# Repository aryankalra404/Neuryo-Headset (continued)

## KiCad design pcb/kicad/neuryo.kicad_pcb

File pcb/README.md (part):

# Neuryo EEG board, rev B (plan)

**Status (5th pass, 11 Nov 2026):** designed in KiCad 10 ([neuryo-rev-b/](neuryo-rev-b/)), ERC/DRC/netlist checked after every step, firmware written, order files drafted ([order-draft-do-not-order/](neuryo-rev-b/review/order-draft-do-not-order/)), **not ordered**: the owner's checks before paying are in [checklist section 9](neuryo-rev-b/REVIEW-CHECKLIST.md) ([5th-pass changes](neuryo-rev-b/CHANGES.md#5th-pass-11-nov-2026), [assembly notes and placement-preview list](neuryo-rev-b/ASSEMBLY.md)). Rev B copies the analog half of a proven open board and adds a ready-made ESP32 board. Rev A (30 Oct, the v3 board: Cyton circuit, auto-routed, 100 × 80 mm, DevKit on sockets) is removed from this folder; it is in the git history (commit `14b8c37` and earlier).

| Folder | What is in it |
|---|---|
| [neuryo-rev-b/](neuryo-rev-b/) | Rev B in KiCad 10: project, [change list](neuryo-rev-b/CHANGES.md), [review checklist](neuryo-rev-b/REVIEW-CHECKLIST.md), renders, ERC/DRC reports, netlist and copper diffs against the reference, the reference imported into KiCad, and the scripts that made the edits |
| [low-cost-eeg/](low-cost-eeg/) | The upstream repo, complete (hardware, production files, firmware, receiver, case STLs, docs). The design rev B copies: [Low-Cost-EEG](https://github.com/XavierAsghar/Low-Cost-EEG) by Xavier Asghar, commit `3730d31` (12 Aug 2026). GPL-3.0 ([LICENSE](low-cost-eeg/LICENSE)); what was left out is listed in its [NOTICE](low-cost-eeg/NOTICE.md). **Do not order from `low-cost-eeg/Production_Files/NC Drill` as it is:** its drill coordinates are offset from the Gerbers (round-hole centres span x 64.4–158.9 mm, y 51.7–97.9 mm, while the Gerber outline is 0–100 × 0–50 mm) |

## Why this board
- **Same chips as ours:** ADS1299 (8 channels, SRB2 reference, bias drive) and an ESP32-S3, battery powered, 4-layer.
- **Built and used:** it recorded ECG, EMG, eyes-closed alpha, SSVEPs and P300s (Final Report, chapter 5), and a second person [rebuilt it](https://github.com/agteo/diy-eeg-mac) from the same files and recorded alpha.
- **Measured:** 1.10 µVpp input-referred noise with the inputs shorted, on the board itself (Final Report, section 6.1; the 2 µVpp earlier in the report is TI's evaluation board). The ADS1299 datasheet gives 1.13 µVpp typical at gain 12, 250 SPS.
- **Its analog section follows the OpenBCI Cyton**, like rev A did.

## What rev B copies unchanged (the analog half, about 55 × 50 mm)
In the KiCad rev B the analog half (x < 56 mm) and the LM27762 block are unchanged apart from the review changes; the TPS7A20 and its two capacitors had to be re-laid out in a strip under the LM27762 block (see [CHANGES B4](neuryo-rev-b/CHANGES.md)).

Placement, routing, ground pours and stitching kept as in the reference, left half of its board:
- Electrode inputs: 2.54 mm pin headers, 8 differential pairs, BIAS, SRB2.
- TPD4E1B06 ESD diodes, then 2.2 kΩ + 1 nF C0G low-pass on every input.
- ADS1299 with its decoupling, bipolar ±2.5 V mode.
- LM27762 charge-pump LDO for ±2.5 V; TPS7A20 low-noise LDO giving the ADS1299 its own 3.3 V.
- Stack-up: signal / ground / segmented power / signal; no split ground plane; analog left, digital right.

## What rev B changes (the digital half)
| Removed from the reference | Added in rev B |
|---|---|
| ESP32-S3-WROOM-1 and its 3.3 V LDO | Seeed XIAO ESP32-S3, soldered flat on castellated pads (Seeed's KiCad footprint); its 3V3 feeds the digital parts |
| USB-C, USB ESD, boot and reset buttons | The XIAO's own USB-C and buttons |
| USB / battery selector switch | Battery on/off slide switch (C&K PCM12, right edge); battery JST-PH (right edge) to the XIAO's BAT pads (the XIAO charges it) and to the LM27762 and TPS7A20 inputs |
| UART header | J6: earlobe MAX30102 and J7: BMI270, 1×4 headers on one I²C bus (the forehead MAX30102 header J8 was dropped) |
| | Battery divider (2 × 220 kΩ + 100 nF) to an ADC pin; USB-present divider; USB interlock (Q1, R37, R38) |
| | Outline 77 × 50 mm (the LM27762 block is kept in place, so 70 was not reachable), 2 mounting holes, for the v6 left pod |

## XIAO pin map
Final map in [neuryo-rev-b/CHANGES.md](neuryo-rev-b/CHANGES.md#final-xiao-pin-map-replaces-the-draft-in-pcbreadmemd). SPI on D1–D5 (330 Ω in series on SCLK, MOSI, CS since the 4th pass), battery on D0, I²C on D7/D8 (4.7 k pull-ups), USB sense on D9, ADS1299 RESET on D10 (4th pass); START and PWDN are tied (change 4).

## Review (8 Nov 2026): changes needed before ordering
Checked against the reference schematic and firmware (upstream `main.cpp`), the ADS1299 datasheet and the Seeed XIAO ESP32-S3 wiki.

| # | Change | Why |
|---|---|---|
| 1 | **Reference through SRB2, filtered.** Move R27 (2.2 kΩ) and C31 (1 nF) from SRB1 (pin 17) to SRB2 (pin 18, the next pin); leave SRB1 open and drop the header's direct SRB2 line. | On the reference, the REF header goes through R27/C31 to SRB1, but its SRB2 pin runs straight to the ADS1299 with no series resistor or filter. Upstream firmware uses SRB1 (MISC1 = 0x20, electrodes on the P inputs). D25 needs SRB2 so channel 8 can run differential (ECG). |
| 2 | **Analog off while USB is plugged in.** XIAO 5V pin → 2N7002 gate (100 kΩ to ground); its drain pulls the LM27762 EN+/EN− and TPS7A20 EN net (100 kΩ up to the battery) low. D9 (GPIO8) reads USB-present through a divider; firmware keeps the SPI pins high-impedance then. | Recording only on battery isolates the patient from mains. The XIAO's 5V pin is live only on USB (Seeed). The reference author lists this as the top-priority fix (Final Report 6.4). |
| 3 | **Charge batteries outside the headset.** Removable JST-PH cell, a separate charger and a spare. | The XIAO ESP32-S3 charges at 50 mA (Seeed), about 20 h for 1000 mAh. |
| 4 | **Pins with no XIAO GPIO:** START to ground through 10 kΩ (use the START command), RESET and PWDN to DVDD through 10 kΩ (RESET command), CLKSEL high as on the reference. Firmware sets BIASREF_INT = 1 (CONFIG3), as upstream does; the BIASREF pin is tied to AVSS on this board. | Datasheet: keep START low when using the command; mode pins through ≥ 10 kΩ. Upstream issue #1 (RESET on GPIO8 vs GPIO14) does not apply: rev B has no RESET GPIO. |
| 5 | **BIAS series resistor 51 kΩ** (R10, was 2.2 kΩ). Inputs stay 2.2 kΩ for the prototype; revisit with the test lab. | The bias amplifier can source 1.1 mA (datasheet) against DC patient-current limits of 10 µA normal and 50 µA single fault. TI's own figures show 51 kΩ patient-protection resistors. A 51 kΩ input resistor would add about 0.23 µVrms of noise, so not on the inputs yet. The reference author found the bias drive gave no benefit on ECG, so test with it on and off. |
| 6 | **Keep the bottom-side parts.** The 17 input filter capacitors, R32–R35, C49 and D6 are on the bottom: order two-sided assembly or hand-solder them; don't move analog parts. | The analog layout is the part that is proven. |
| 7 | **XIAO flat on the board:** its BAT pads are underneath, so the footprint needs matching pads and hot-air or hot-plate soldering; no copper or vias under its other pads. | Castellated edges can be hand-soldered, the underside cannot. |
| 8 | **Stock check:** ADS1299IPAGR, LM27762DSSR, TPS7A2033PDBVR, TPD4E1B06DCKR at LCSC/JLCPCB. | One order. |

## Channel map (v4)
Electrodes on the N inputs with M1 on SRB2 (through the filtered REF path, change 1), as on the Cyton: ch 1 Fp1, ch 2 Fp2, ch 3 Fz, ch 4 Pz, ch 5 M2, ch 6 eye, ch 7 free (no Cz pod anywhere, decision D36, v6.3), ch 8 ECG (SRB2 off, differential, test kit). BIAS to Fpz.

## Steps
1. ~~Import the reference into KiCad and check it~~ (done 8 Nov: BOM references and board/schematic connectivity match; sheet-by-sheet PDF comparison is on the checklist).
2. ~~Remove the module side; add the XIAO, J6, J7, interlock, dividers~~ (done; see the change list).
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
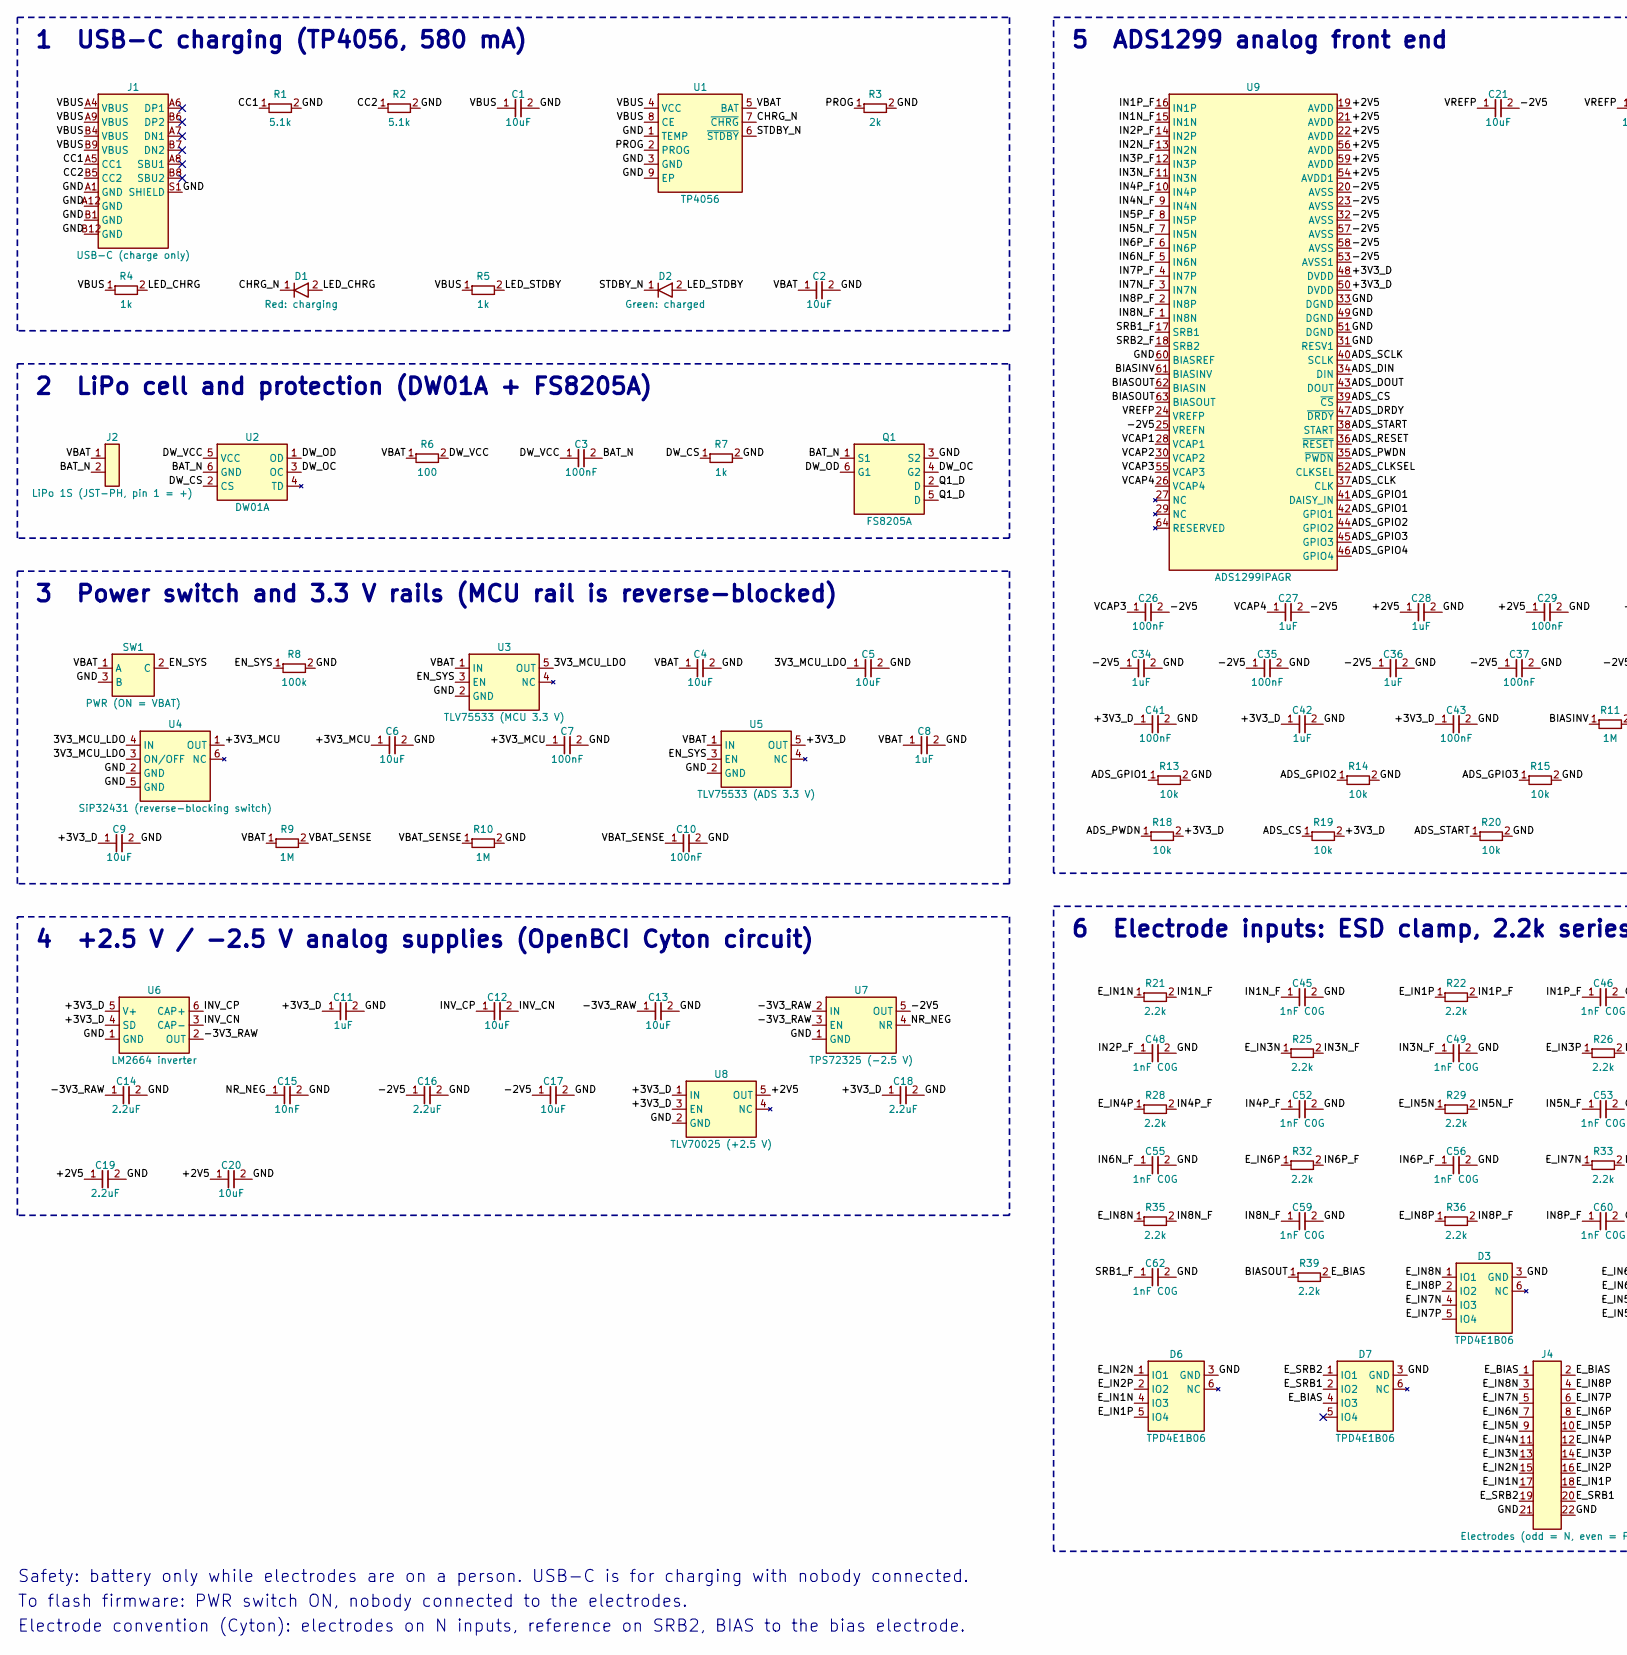
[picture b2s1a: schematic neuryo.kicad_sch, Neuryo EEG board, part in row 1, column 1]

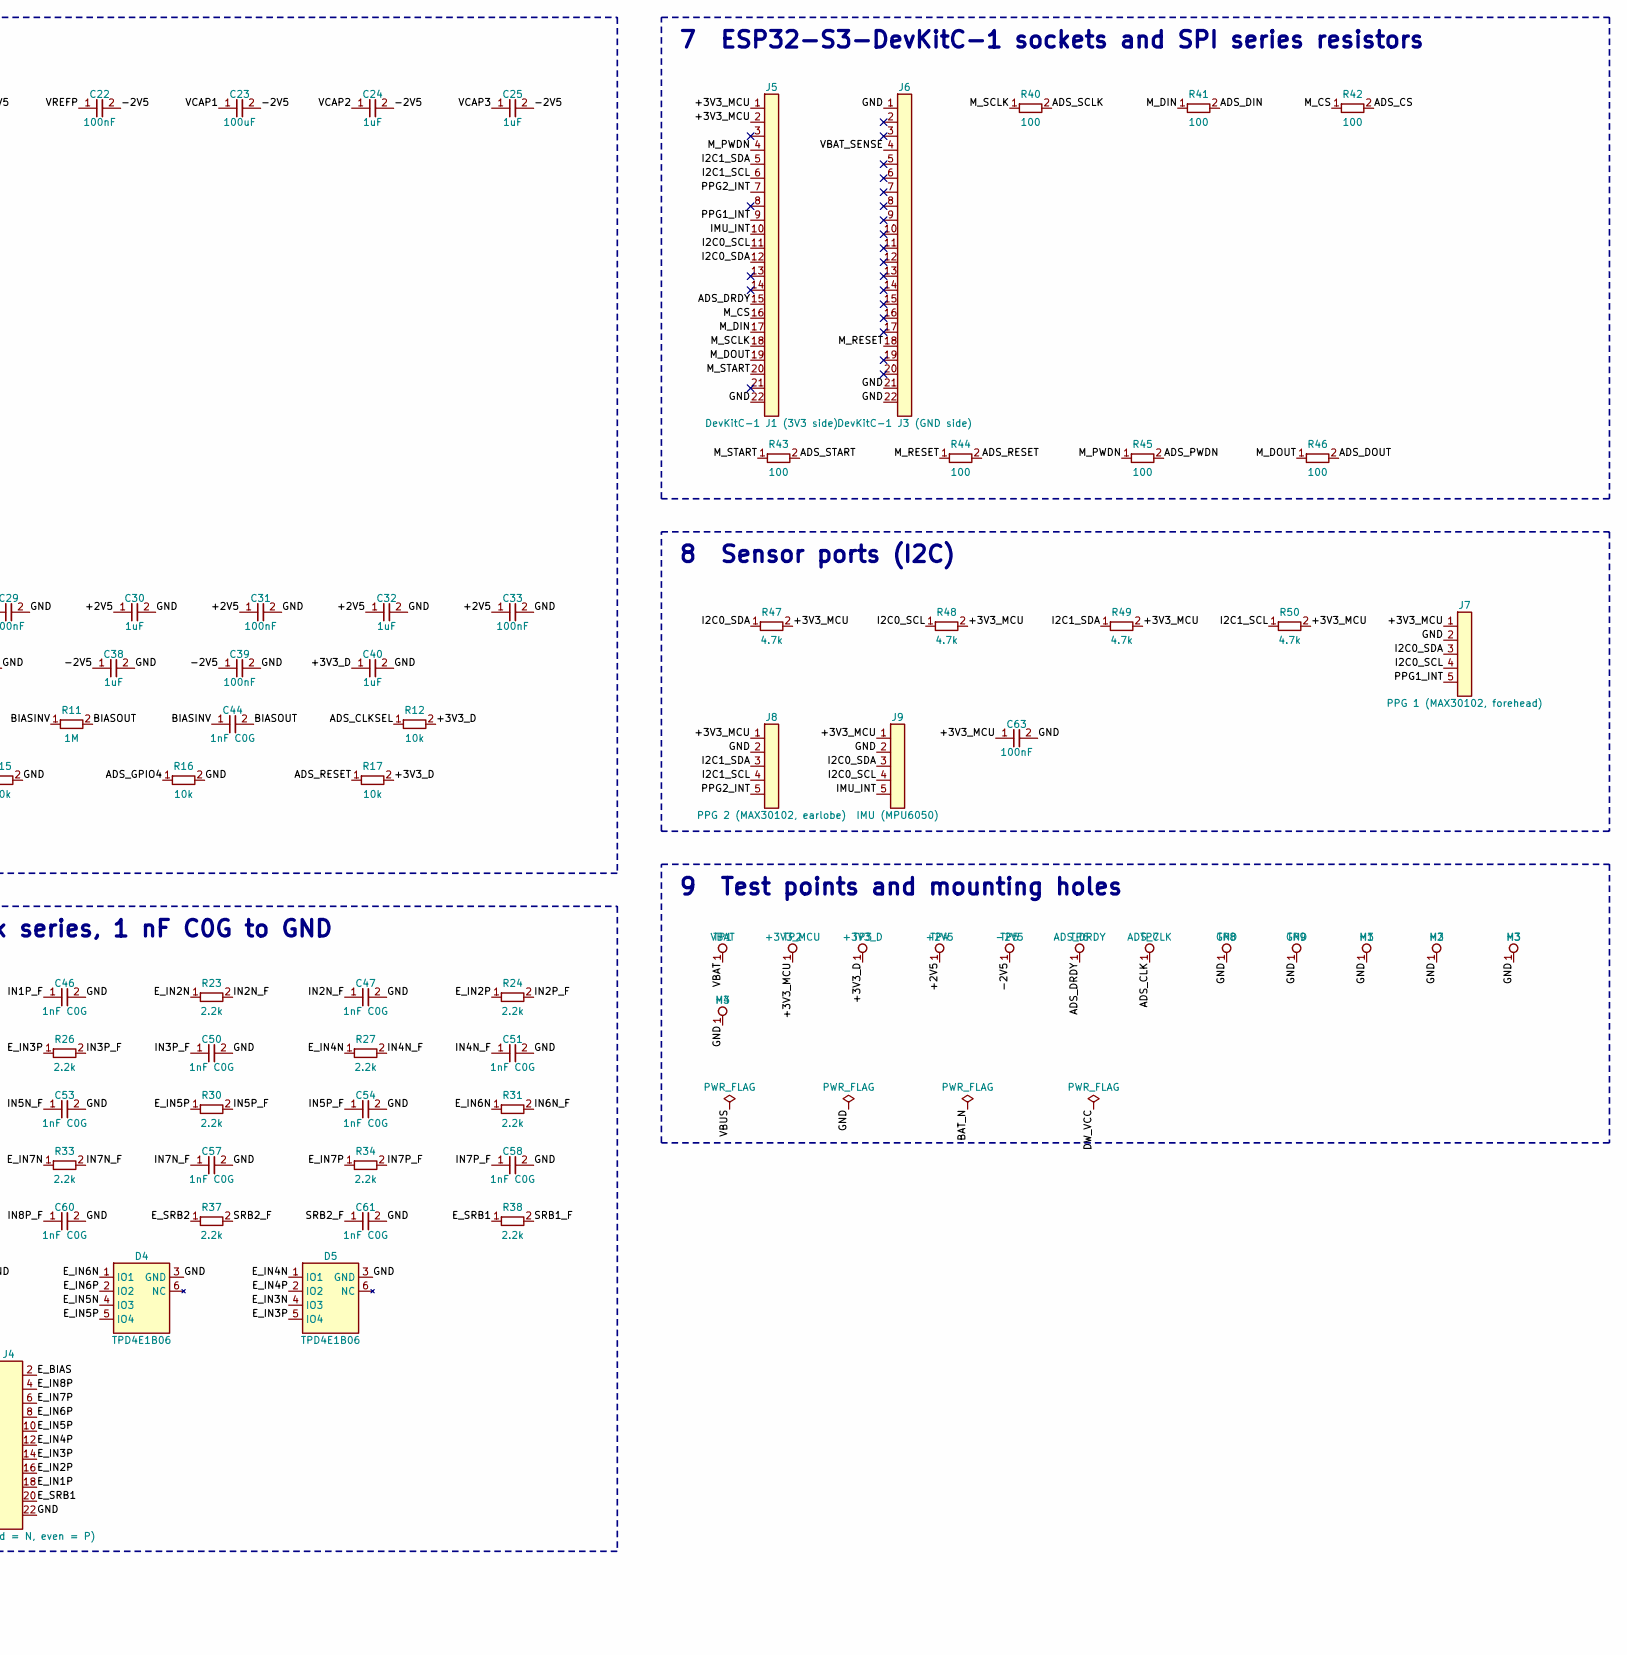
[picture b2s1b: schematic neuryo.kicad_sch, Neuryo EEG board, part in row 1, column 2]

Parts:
C1, C2, C4, C21: 10uF; C_0805_2012Metric; LCSC C15850
C3, C7, C10, C22, C26, C29, C31, C33, C35, C37, C39, C41, C43, C63: 100nF; C_0603_1608Metric; LCSC C14663
C5, C6, C9, C12, C13, C17, C20: 10uF; C_0603_1608Metric; LCSC C19702
C8, C11, C24, C25, C27, C28, C30, C32, C34, C36, C38, C40, C42: 1uF; C_0603_1608Metric; LCSC C15849
C14, C16, C18, C19: 2.2uF; C_0603_1608Metric; LCSC C23630
C15: 10nF; C_0603_1608Metric; LCSC C57112
C23: 100uF; C_1206_3216Metric; LCSC C15008
C44, C45, C46, C47, C48, C49, C50, C51, C52, C53, C54, C55, C56, C57, C58, C59, C60, C61, C62: 1nF C0G; C_0603_1608Metric; LCSC C163508
D1: Red: charging; LED_0805_2012Metric; MPN NCD0805R1; LCSC C84256
D2: Green: charged; LED_0805_2012Metric; MPN KT-0805G; LCSC C2297
D3, D4, D5, D6, D7: TPD4E1B06; SOT-363_SC-70-6; MPN TPD4E1B06DCKR; LCSC C840093
H1, H2, H3, H4: M3; MountingHole_3.2mm_M3_Pad_Via
J1: USB-C (charge only); USB_C_Receptacle_HRO_TYPE-C-31-M-12; MPN HRO TYPE-C-31-M-12; LCSC C165948
J2: LiPo 1S (JST-PH, pin 1 = +); JST_PH_S2B-PH-SM4-TB_1x02-1MP_P2.00mm_Horizontal; MPN S2B-PH-SM4-TB(LF)(SN); LCSC C295747
J4: Electrodes (odd = N, even = P); PinHeader_2x11_P2.54mm_Vertical
J5: DevKitC-1 J1 (3V3 side); PinSocket_1x22_P2.54mm_Vertical
J6: DevKitC-1 J3 (GND side); PinSocket_1x22_P2.54mm_Vertical
J7: PPG 1 (MAX30102, forehead); PinHeader_1x05_P2.54mm_Vertical
J8: PPG 2 (MAX30102, earlobe); PinHeader_1x05_P2.54mm_Vertical
J9: IMU (MPU6050); PinHeader_1x05_P2.54mm_Vertical
Q1: FS8205A; SOT-23-6; MPN FS8205A; LCSC C908265
R1, R2: 5.1k; R_0603_1608Metric; LCSC C23186
R3: 2k; R_0603_1608Metric; LCSC C22975
R4, R5, R7: 1k; R_0603_1608Metric; LCSC C21190
R6, R40, R41, R42, R43, R44, R45, R46: 100; R_0603_1608Metric; LCSC C22775
R8: 100k; R_0603_1608Metric; LCSC C25803
R9, R10, R11: 1M; R_0603_1608Metric; LCSC C22935
R12, R13, R14, R15, R16, R17, R18, R19, R20: 10k; R_0603_1608Metric; LCSC C25804
R21, R22, R23, R24, R25, R26, R27, R28, R29, R30, R31, R32, R33, R34, R35, R36, R37, R38, R39: 2.2k; R_0603_1608Metric; LCSC C4190
R47, R48, R49, R50: 4.7k; R_0603_1608Metric; LCSC C23162
SW1: PWR (ON = VBAT); SW_SPDT_PCM12; MPN PCM12SMTR; LCSC C221841
TP1: VBAT; TestPoint_Pad_D1.5mm
TP2: +3V3_MCU; TestPoint_Pad_D1.5mm
TP3: +3V3_D; TestPoint_Pad_D1.5mm
TP4: +2V5; TestPoint_Pad_D1.5mm
TP5: -2V5; TestPoint_Pad_D1.5mm
TP6: ADS_DRDY; TestPoint_Pad_D1.5mm
TP7: ADS_CLK; TestPoint_Pad_D1.5mm
TP8, TP9: GND; TestPoint_Pad_D1.5mm
U1: TP4056; SOIC-8-1EP_3.9x4.9mm_P1.27mm_EP2.41x3.3mm; MPN TP4056-42-ESOP8; LCSC C16581
U2: DW01A; SOT-23-6; MPN DW01A; LCSC C351410
U3: TLV75533 (MCU 3.3 V); SOT-23-5; MPN TLV75533PDBVR; LCSC C404027
U4: SiP32431 (reverse-blocking switch); SOT-363_SC-70-6; MPN SIP32431DR3-T1GE3; LCSC C141606
U5: TLV75533 (ADS 3.3 V); SOT-23-5; MPN TLV75533PDBVR; LCSC C404027
U6: LM2664 inverter; SOT-23-6; MPN LM2664M6X/NOPB; LCSC C108573
U7: TPS72325 (-2.5 V); SOT-23-5; MPN TPS72325DBVR; LCSC C69932
U8: TLV70025 (+2.5 V); SOT-23-5; MPN TLV70025DDCR; LCSC C19619
U9: ADS1299IPAGR; TQFP-64_10x10mm_P0.5mm; MPN ADS1299IPAGR; LCSC C476817

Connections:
/3V3_MCU_LDO: C5.1, U3.5 (OUT), U4.3 (ON/OFF), U4.4 (IN)
/+2V5: C19.1, C20.1, C28.1, C29.1, C30.1, C31.1, C32.1, C33.1, TP4.1, U8.5 (OUT), U9.19 (AVDD), U9.21 (AVDD), U9.22 (AVDD), U9.54 (AVDD1), U9.56 (AVDD), U9.59 (AVDD)
/+3V3_D: C9.1, C11.1, C18.1, C40.1, C41.1, C42.1, C43.1, R12.2, R17.2, R18.2, R19.2, TP3.1, U5.5 (OUT), U6.4 (SD), U6.5 (V+), U8.1 (IN), U8.3 (EN), U9.48 (DVDD), U9.50 (DVDD)
/+3V3_MCU: C6.1, C7.1, C63.1, J5.1, J5.2, J7.1, J8.1, J9.1, R47.2, R48.2, R49.2, R50.2, TP2.1, U4.1 (OUT)
/-2V5: C16.1, C17.1, C21.2, C22.2, C23.2, C24.2, C25.2, C26.2, C27.2, C34.1, C35.1, C36.1, C37.1, C38.1, C39.1, TP5.1, U7.5 (OUT), U9.20 (AVSS), U9.23 (AVSS), U9.25 (VREFN), U9.32 (AVSS), U9.53 (AVSS1), U9.57 (AVSS), U9.58 (AVSS)
/-3V3_RAW: C13.1, C14.1, U6.2 (OUT), U7.2 (IN), U7.3 (EN)
/ADS_CLK: TP7.1, U9.37 (CLK)
/ADS_CLKSEL: R12.1, U9.52 (CLKSEL)
/ADS_CS: R19.1, R42.2, U9.39 (~CS)
/ADS_DIN: R41.2, U9.34 (DIN)
/ADS_DOUT: R46.2, U9.43 (DOUT)
/ADS_DRDY: J5.15, TP6.1, U9.47 (~DRDY)
/ADS_GPIO1: R13.1, U9.41 (DAISY_IN), U9.42 (GPIO1)
/ADS_GPIO2: R14.1, U9.44 (GPIO2)
/ADS_GPIO3: R15.1, U9.45 (GPIO3)
/ADS_GPIO4: R16.1, U9.46 (GPIO4)
/ADS_PWDN: R18.1, R45.2, U9.35 (~PWDN)
/ADS_RESET: R17.1, R44.2, U9.36 (~RESET)
/ADS_SCLK: R40.2, U9.40 (SCLK)
/ADS_START: R20.1, R43.2, U9.38 (START)
/BAT_N: C3.2, J2.2, Q1.1 (S1), U2.6 (GND)
/BIASINV: C44.1, R11.1, U9.61 (BIASINV)
/BIASOUT: C44.2, R11.2, R39.1, U9.62 (BIASIN), U9.63 (BIASOUT)
/CC1: J1.A5 (CC1), R1.1
/CC2: J1.B5 (CC2), R2.1
/CHRG_N: D1.1 (K), U1.7 (~CHRG)
/DW_CS: R7.1, U2.2 (CS)
/DW_OC: Q1.4 (G2), U2.3 (OC)
/DW_OD: Q1.6 (G1), U2.1 (OD)
/DW_VCC: C3.1, R6.2, U2.5 (VCC)
/EN_SYS: R8.1, SW1.2 (C), U3.3 (EN), U5.3 (EN)
/E_BIAS: D7.4 (IO3), J4.1, J4.2, R39.2
/E_IN1N: D6.4 (IO3), J4.17, R21.1
/E_IN1P: D6.5 (IO4), J4.18, R22.1
/E_IN2N: D6.1 (IO1), J4.15, R23.1
/E_IN2P: D6.2 (IO2), J4.16, R24.1
/E_IN3N: D5.4 (IO3), J4.13, R25.1
/E_IN3P: D5.5 (IO4), J4.14, R26.1
/E_IN4N: D5.1 (IO1), J4.11, R27.1
/E_IN4P: D5.2 (IO2), J4.12, R28.1
/E_IN5N: D4.4 (IO3), J4.9, R29.1
/E_IN5P: D4.5 (IO4), J4.10, R30.1
/E_IN6N: D4.1 (IO1), J4.7, R31.1
/E_IN6P: D4.2 (IO2), J4.8, R32.1
/E_IN7N: D3.4 (IO3), J4.5, R33.1
/E_IN7P: D3.5 (IO4), J4.6, R34.1
/E_IN8N: D3.1 (IO1), J4.3, R35.1
/E_IN8P: D3.2 (IO2), J4.4, R36.1
/E_SRB1: D7.2 (IO2), J4.20, R38.1
/E_SRB2: D7.1 (IO1), J4.19, R37.1
/GND: C1.2, C2.2, C4.2, C5.2, C6.2, C7.2, C8.2, C9.2, C10.2, C11.2, C13.2, C14.2, C15.2, C16.2, C17.2, C18.2, C19.2, C20.2, C28.2, C29.2, C30.2, C31.2, C32.2, C33.2, C34.2, C35.2, C36.2, C37.2, C38.2, C39.2, C40.2, C41.2, C42.2, C43.2, C45.2, C46.2, C47.2, C48.2, C49.2, C50.2, C51.2, C52.2, C53.2, C54.2, C55.2, C56.2, C57.2, C58.2, C59.2, C60.2, C61.2, C62.2, C63.2, D3.3 (GND), D4.3 (GND), D5.3 (GND), D6.3 (GND), D7.3 (GND), H1.1, H2.1, H3.1, H4.1, J1.A1 (GND), J1.A12 (GND), J1.B1 (GND), J1.B12 (GND), J1.S1 (SHIELD), J4.21, J4.22, J5.22, J6.1, J6.21, J6.22, J7.2, J8.2, J9.2, Q1.3 (S2), R1.2, R2.2, R3.2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
/I2C0_SCL: J5.11, J7.4, J9.4, R48.1
/I2C0_SDA: J5.12, J7.3, J9.3, R47.1
/I2C1_SCL: J5.6, J8.4, R50.1
/I2C1_SDA: J5.5, J8.3, R49.1
/IMU_INT: J5.10, J9.5
/IN1N_F: C45.1, R21.2, U9.15 (IN1N)
/IN1P_F: C46.1, R22.2, U9.16 (IN1P)
/IN2N_F: C47.1, R23.2, U9.13 (IN2N)
/IN2P_F: C48.1, R24.2, U9.14 (IN2P)
/IN3N_F: C49.1, R25.2, U9.11 (IN3N)
/IN3P_F: C50.1, R26.2, U9.12 (IN3P)
/IN4N_F: C51.1, R27.2, U9.9 (IN4N)
/IN4P_F: C52.1, R28.2, U9.10 (IN4P)
/IN5N_F: C53.1, R29.2, U9.7 (IN5N)
/IN5P_F: C54.1, R30.2, U9.8 (IN5P)
/IN6N_F: C55.1, R31.2, U9.5 (IN6N)
/IN6P_F: C56.1, R32.2, U9.6 (IN6P)
/IN7N_F: C57.1, R33.2, U9.3 (IN7N)
/IN7P_F: C58.1, R34.2, U9.4 (IN7P)
/IN8N_F: C59.1, R35.2, U9.1 (IN8N)
/IN8P_F: C60.1, R36.2, U9.2 (IN8P)
/INV_CN: C12.2, U6.3 (CAP-)
/INV_CP: C12.1, U6.6 (CAP+)
/LED_CHRG: D1.2 (A), R4.2
/LED_STDBY: D2.2 (A), R5.2
/M_CS: J5.16, R42.1
/M_DIN: J5.17, R41.1
/M_DOUT: J5.19, R46.1
/M_PWDN: J5.4, R45.1
/M_RESET: J6.18, R44.1
/M_SCLK: J5.18, R40.1
/M_START: J5.20, R43.1
/NR_NEG: C15.1, U7.4 (NR)
/PPG1_INT: J5.9, J7.5
/PPG2_INT: J5.7, J8.5
/PROG: R3.1, U1.2 (PROG)
/Q1_D: Q1.2 (D), Q1.5 (D)
/SRB1_F: C62.1, R38.2, U9.17 (SRB1)
/SRB2_F: C61.1, R37.2, U9.18 (SRB2)
/STDBY_N: D2.1 (K), U1.6 (~STDBY)
/VBAT: C2.1, C4.1, C8.1, J2.1, R6.1, R9.1, SW1.1 (A), TP1.1, U1.5 (BAT), U3.1 (IN), U5.1 (IN)
/VBAT_SENSE: C10.1, J6.4, R9.2, R10.1
/VBUS: C1.1, J1.A4 (VBUS), J1.A9 (VBUS), J1.B4 (VBUS), J1.B9 (VBUS), R4.1, R5.1, U1.4 (VCC), U1.8 (CE)
/VCAP1: C23.1, U9.28 (VCAP1)
/VCAP2: C24.1, U9.30 (VCAP2)
/VCAP3: C25.1, C26.1, U9.55 (VCAP3)
/VCAP4: C27.1, U9.26 (VCAP4)
/VREFP: C21.1, C22.1, U9.24 (VREFP)

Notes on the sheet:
1 USB-C charging (TP4056, 580 mA)
2 LiPo cell and protection (DW01A + FS8205A)
3 Power switch and 3.3 V rails (MCU rail is reverse-blocked)
4 +2.5 V / -2.5 V analog supplies (OpenBCI Cyton circuit)
5 ADS1299 analog front end
6 Electrode inputs: ESD clamp, 2.2k series, 1 nF C0G to GND
7 ESP32-S3-DevKitC-1 sockets and SPI series resistors
8 Sensor ports (I2C)
9 Test points and mounting holes
Safety: battery only while electrodes are on a person. USB-C is for charging with nobody connected.
To flash firmware: PWR switch ON, nobody connected to the electrodes.
Electrode convention (Cyton): electrodes on N inputs, reference on SRB2, BIAS to the bias electrode.

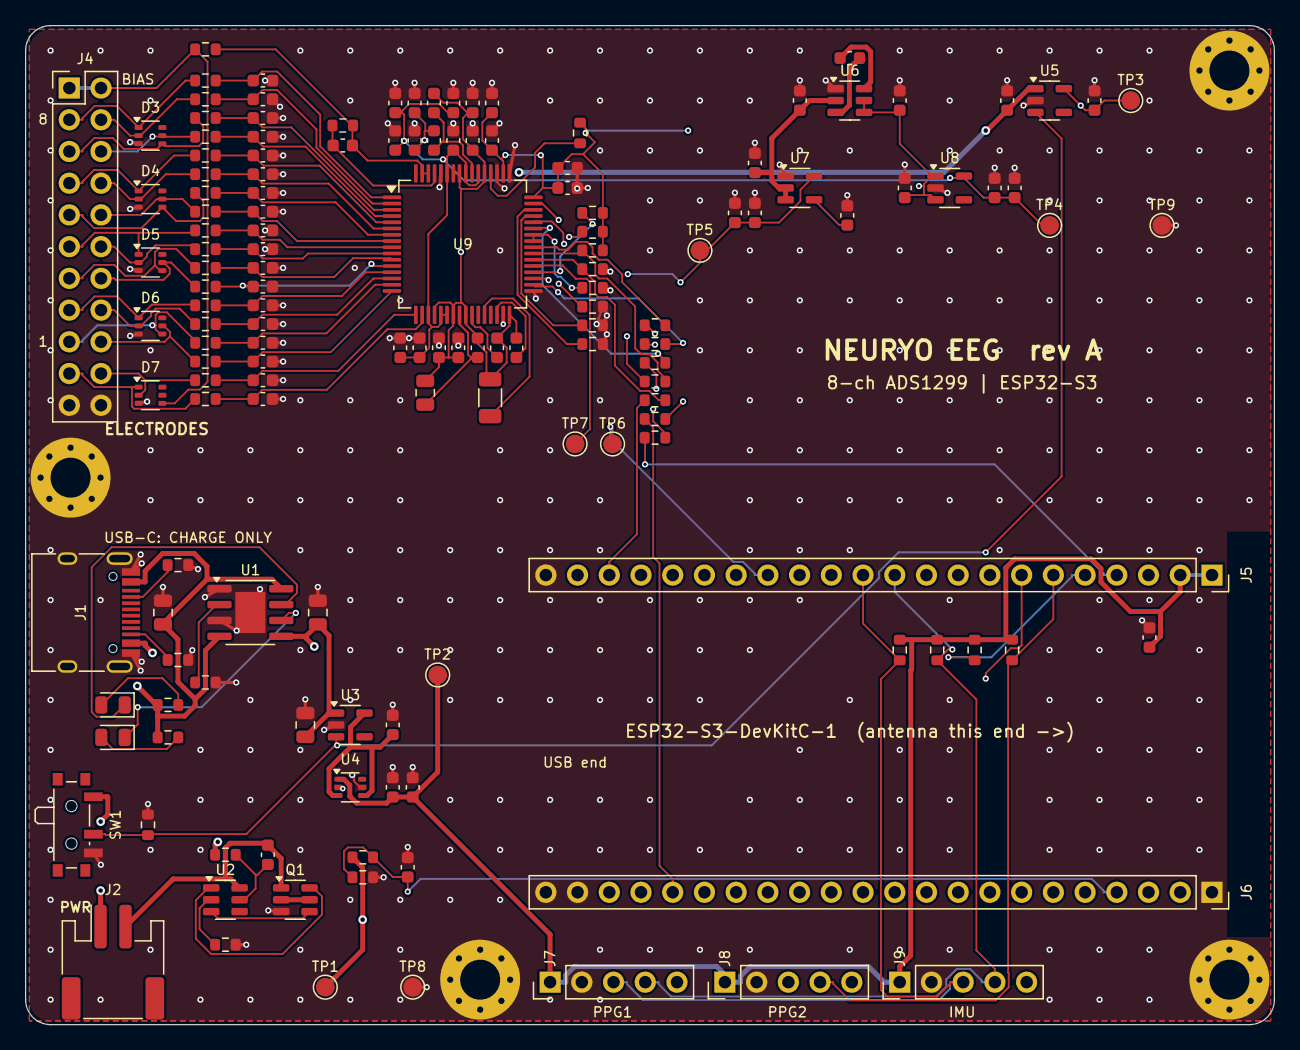
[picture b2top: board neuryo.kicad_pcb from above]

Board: 4 copper layers, 100.0 x 80.0 mm, 152 parts (0 on the bottom side), 99 nets.

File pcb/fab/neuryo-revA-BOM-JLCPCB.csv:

Comment,Designator,Footprint,LCSC Part #
10uF,"C1,C2,C4,C21",C_0805_2012Metric,C15850
100nF,"C3,C7,C10,C22,C26,C29,C31,C33,C35,C37,C39,C41,C43,C63",C_0603_1608Metric,C14663
10uF,"C5,C6,C9,C12,C13,C17,C20",C_0603_1608Metric,C19702
1uF,"C8,C11,C24,C25,C27,C28,C30,C32,C34,C36,C38,C40,C42",C_0603_1608Metric,C15849
2.2uF,"C14,C16,C18,C19",C_0603_1608Metric,C23630
10nF,C15,C_0603_1608Metric,C57112
100uF,C23,C_1206_3216Metric,C15008
1nF C0G,"C44,C45,C46,C47,C48,C49,C50,C51,C52,C53,C54,C55,C56,C57,C58,C59,C60,C61,C62",C_0603_1608Metric,C163508
NCD0805R1,D1,LED_0805_2012Metric,C84256
KT-0805G,D2,LED_0805_2012Metric,C2297
TPD4E1B06DCKR,"D3,D4,D5,D6,D7",SOT-363_SC-70-6,C840093
HRO TYPE-C-31-M-12,J1,USB_C_Receptacle_HRO_TYPE-C-31-M-12,C165948
S2B-PH-SM4-TB(LF)(SN),J2,JST_PH_S2B-PH-SM4-TB_1x02-1MP_P2.00mm_Horizontal,C295747
FS8205A,Q1,SOT-23-6,C908265
5.1k,"R1,R2",R_0603_1608Metric,C23186
2k,R3,R_0603_1608Metric,C22975
1k,"R4,R5,R7",R_0603_1608Metric,C21190
100,"R6,R40,R41,R42,R43,R44,R45,R46",R_0603_1608Metric,C22775
100k,R8,R_0603_1608Metric,C25803
1M,"R9,R10,R11",R_0603_1608Metric,C22935
10k,"R12,R13,R14,R15,R16,R17,R18,R19,R20",R_0603_1608Metric,C25804
2.2k,"R21,R22,R23,R24,R25,R26,R27,R28,R29,R30,R31,R32,R33,R34,R35,R36,R37,R38,R39",R_0603_1608Metric,C4190
4.7k,"R47,R48,R49,R50",R_0603_1608Metric,C23162
PCM12SMTR,SW1,SW_SPDT_PCM12,C221841
TP4056-42-ESOP8,U1,SOIC-8-1EP_3.9x4.9mm_P1.27mm_EP2.41x3.3mm,C16581
DW01A,U2,SOT-23-6,C351410
TLV75533PDBVR,"U3,U5",SOT-23-5,C404027
SIP32431DR3-T1GE3,U4,SOT-363_SC-70-6,C141606
LM2664M6X/NOPB,U6,SOT-23-6,C108573
TPS72325DBVR,U7,SOT-23-5,C69932
TLV70025DDCR,U8,SOT-23-5,C19619
ADS1299IPAGR,U9,TQFP-64_10x10mm_P0.5mm,C476817

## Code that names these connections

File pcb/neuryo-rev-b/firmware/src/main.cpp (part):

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ADS1299 ADS;

// XIAO ESP32-S3 pins (rev B schematic, U6). Dn -> GPIO from the XIAO_ESP32S3 variant in arduino-esp32.
#define VBAT_SENSE_PIN 1    // D0: battery through 220k/220k, 100 nF
#define DRDY_PIN       2    // D1
#define CS_PIN         3    // D2 (10k pull-up to DVDD on the board, R28)
#define MOSI_PIN       4    // D3 -> ADS1299 DIN
#define SCK_PIN        5    // D4
#define MISO_PIN       6    // D5 <- ADS1299 DOUT
#define I2C_SDA_PIN    7    // D8 -> J6 (MAX30102), J7 (BMI270)
#define I2C_SCL_PIN    44   // D7
#define USB_SENSE_PIN  8    // D9: XIAO 5V through 100k/150k, high = USB present = ADS1299 unpowered (interlock)
#define BOOT_BUTTON_PIN 0
// 4th pass: D10 (GPIO9) -> ADS1299 RESET (R30 10k pull-up to DVDD stays). Driven open-drain only, never high, so it
// cannot back-power the ADS1299 when the analog side is off. Not passed to the library (it would drive it push-pull).
#define ADS_RESET_PIN  9    // D10
static_assert(D10 == ADS_RESET_PIN, "XIAO D10 must be GPIO9 (rev B 4th pass pin map)");
// START has no GPIO: pulled down (R36 10k), START command used. PWDN pulled up (10k).
#define NO_PIN        -1

// Bench build (env xiao_esp32s3_bench, -D BENCH_NO_INTERLOCK): USB_SENSE is ignored and the ADS1299 starts on USB,
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  pinMode(SCK_PIN, INPUT);
  pinMode(MOSI_PIN, INPUT);
  pinMode(CS_PIN, INPUT);
  pinMode(DRDY_PIN, INPUT);
  pinMode(ADS_RESET_PIN, INPUT);           // R30 holds RESET high; only ever pulled low (open-drain)
  pinMode(USB_SENSE_PIN, INPUT);           // divider drives it; no internal pull
#ifndef BENCH_NO_INTERLOCK
  attachInterrupt(digitalPinToInterrupt(USB_SENSE_PIN), usbSenseISR, CHANGE);
#endif

  Serial.begin(115200);
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  analogReadResolution(12);

  // I2C: earlobe MAX30102 (0x57) and BMI270 (0x68 or 0x69) on J6/J7. 4.7k pull-ups to the XIAO 3V3 on the board (R46, R47).
  Wire.begin(I2C_SDA_PIN, I2C_SCL_PIN, 400000);
  i2cFound = "";
  for (uint8_t a = 0x08; a < 0x78; a++) {
    Wire.beginTransmission(a);
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#ifdef BENCH_NO_INTERLOCK
  adsStart();
#else
  if (digitalRead(USB_SENSE_PIN) == HIGH) {
    Serial.println("USB present: analog side is off (interlock). Unplug USB to record.");
  } else {
    adsStart();
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  if (usbEvent) {
    usbEvent = false;
    delay(20);                                           // let the divider and the EN net settle
    bool usb = digitalRead(USB_SENSE_PIN) == HIGH;
    if (usb && adsStarted) {
      adsStop();
      Serial.println("USB plugged in: ADS1299 stopped, SPI ended, lines released.");
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// Returns false, with adsRunning and adsStarted false and the SPI lines released (SPI ended), if the ID register does
// not read as an ADS1299.
bool adsStart() {
  ADS.setup(DRDY_PIN, CS_PIN, SCK_PIN, MISO_PIN, MOSI_PIN, NO_PIN, NO_PIN);   // waits tPOR, then RESET command
  adsHardwareReset();
  ADS.RESET();                      // RESET command after the pulse, as before
  delay(1);
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  for (int i = CH1SET; i <= CH7SET; i++) ADS.WREG(i, 0b01101000);  // gain 24, SRB2 closed, normal input
  ADS.WREG(CH8SET, 0b01100000);                                      // gain 24, SRB2 open: differential (ECG)

  attachInterrupt(digitalPinToInterrupt(DRDY_PIN), dataReadyISR, FALLING);
  adsStarted = true;
  adsRunning = true;
  ADS.RDATAC();                     // continuous data mode, then START (command), as the OpenBCI Cyton library does
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// Datasheet: RESET low for at least 2 tCLK (about 1 us at 2.048 MHz); the device is ready 18 tCLK (about 9 us) after
// RESET goes high. 10 us low and 1 ms wait leave a wide margin. Open-drain: the pin only ever sinks; R30 pulls it high.
void adsHardwareReset() {
  digitalWrite(ADS_RESET_PIN, LOW);
  pinMode(ADS_RESET_PIN, OUTPUT_OPEN_DRAIN);
  digitalWrite(ADS_RESET_PIN, LOW);
  delayMicroseconds(10);
  pinMode(ADS_RESET_PIN, INPUT);
  delay(1);
}

void adsStop() {
  adsRunning = false;
  adsStarted = false;
  detachInterrupt(digitalPinToInterrupt(DRDY_PIN));
  ADS.release();                    // SCLK, MOSI, CS -> inputs (the ISR already did this in hardware)
  xQueueReset(packetQueue);
}
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// USB plugged in: the 2N7002 pulls AEN low and the ADS1299 rails collapse within milliseconds. Stop driving SCLK, MOSI
// and CS at once (register write, safe in an ISR) so the ESP32 never back-powers the ADS1299 through its I/O diodes.
void IRAM_ATTR usbSenseISR() {
  if ((REG_READ(GPIO_IN_REG) >> USB_SENSE_PIN) & 1) {   // register read: no flash access from the ISR
    adsRunning = false;
    REG_WRITE(GPIO_ENABLE_W1TC_REG, (1UL << SCK_PIN) | (1UL << MOSI_PIN) | (1UL << CS_PIN));
  }
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}

void updateStatus() {
  uint32_t mv = analogReadMilliVolts(VBAT_SENSE_PIN) * 2;   // 220k / 220k divider
  char s[192];
  snprintf(s, sizeof(s), "usb=%d ads=%d id=%02X vbat=%lu i2c=%s%s", digitalRead(USB_SENSE_PIN) == HIGH, adsRunning ? 1 : 0,
           adsId, (unsigned long)mv, i2cFound.c_str(), BENCH_NOTE);
  Serial.println(s);
  if (pStatus) {
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
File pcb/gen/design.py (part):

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            ("47", "~{DRDY}", "output", "R"), ("38", "START", "input", "R"),
            ("36", "~{RESET}", "input", "R"), ("35", "~{PWDN}", "input", "R"),
            ("52", "CLKSEL", "input", "R"), ("37", "CLK", "bidirectional", "R"),
            ("41", "DAISY_IN", "input", "R"), ("42", "GPIO1", "bidirectional", "R"),
            ("44", "GPIO2", "bidirectional", "R"), ("45", "GPIO3", "bidirectional", "R"),
            ("46", "GPIO4", "bidirectional", "R"),
        ]},
    "TLV75533": {"width": 12.7, "desc": "TI TLV75533PDBV 3.3 V 500 mA LDO", "pins": [
        ("1", "IN", "power_in", "L"), ("3", "EN", "input", "L"), ("2", "GND", "power_in", "L"),
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
# ================================================================ 5. ADS1299
S = "ADS1299"
# DAISY_IN (41) is tied to GPIO1 (42) and held low by GPIO1's 10k pull-down (no daisy chain)
ads = {
    "16": "IN1P_F", "15": "IN1N_F", "14": "IN2P_F", "13": "IN2N_F", "12": "IN3P_F", "11": "IN3N_F",
    "10": "IN4P_F", "9": "IN4N_F", "8": "IN5P_F", "7": "IN5N_F", "6": "IN6P_F", "5": "IN6N_F",
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    "48": "+3V3_D", "50": "+3V3_D", "33": GND, "49": GND, "51": GND, "31": GND,
    "40": "ADS_SCLK", "34": "ADS_DIN", "43": "ADS_DOUT", "39": "ADS_CS", "47": "ADS_DRDY",
    "38": "ADS_START", "36": "ADS_RESET", "35": "ADS_PWDN", "52": "ADS_CLKSEL", "37": "ADS_CLK",
    "41": "ADS_GPIO1", "42": "ADS_GPIO1", "44": "ADS_GPIO2", "45": "ADS_GPIO3", "46": "ADS_GPIO4",
}
part("U9", "ADS1299", "ADS1299IPAGR", "TQFP64", ads, "C476817", "ADS1299IPAGR", S)
# reference and internal regulator caps (datasheet fig. 78)
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C("1nF C0G", "BIASINV", "BIASOUT", S)
# static configuration
R("10k", "ADS_CLKSEL", "+3V3_D", S)          # internal oscillator
for g in ("ADS_GPIO1", "ADS_GPIO2", "ADS_GPIO3", "ADS_GPIO4"):
    R("10k", g, GND, S)
R("10k", "ADS_RESET", "+3V3_D", S)
R("10k", "ADS_PWDN", "+3V3_D", S)
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
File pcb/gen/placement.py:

"""Component placement for the Neuryo board (board-local mm, origin top-left, y down).

Board 100 x 80 mm. Zones:
  analog  : y 0..38   electrode header -> ESD -> RC filters -> ADS1299 -> analog supplies
  power   : x 0..35, y 38..80   USB-C, charger, battery, protection, switch, MCU LDO
  digital : x 36..100, y 38..80 ESP32-S3-DevKitC-1 on sockets, I2C pull-ups, sensor headers
"""
import design as D

BOARD_W, BOARD_H = 100.0, 80.0
P = {}  # ref -> (x, y, rot, side)


def at(ref, x, y, rot=0, side="F"):
    P[ref] = (x, y, rot, side)


def refs(pred):
    return [p["ref"] for p in D.PARTS if pred(p)]


def find(value=None, nets=None, sym=None, section=None):
    out = []
    for p in D.PARTS:
        if sym and p["sym"] != sym:
            continue
        if value and p["value"] != value:
            continue
        if section and p["section"] != section:
            continue
        if nets and sorted(n for n in p["nets"].values() if n) != sorted(nets):
            continue
        out.append(p["ref"])
    return out


def one(**kw):
    r = find(**kw)
    assert len(r) >= 1, kw
    return r


_used = set()
def take(**kw):
    for r in find(**kw):
        if r not in _used:
            _used.add(r)
            return r
    raise KeyError(kw)

# ---------------------------------------------------------------- analog: electrode header and inputs
at("J4", 3.5, 5.0, 0)                       # pin 1 top-left; rows go down 2.54 mm
at("D3", 10.0, 8.81); at("D4", 10.0, 13.89); at("D5", 10.0, 18.97); at("D6", 10.0, 24.05)
at("D7", 10.0, 29.6)

order = []
for ch in range(8, 0, -1):
    order += [f"IN{ch}N", f"IN{ch}P"]
order += ["SRB1", "SRB2"]
for i, ln in enumerate(order):
    y = 4.4 + i * 1.5
    at(take(value="2.2k", nets=[f"E_{ln}", f"{ln}_F"]), 14.4, y, 0)
    at(take(value="1nF C0G", nets=[f"{ln}_F", "GND"]), 19.0, y, 0)
at(take(value="2.2k", nets=["BIASOUT", "E_BIAS"]), 14.4, 1.9, 180)

# ---------------------------------------------------------------- ADS1299 and its local parts
AX, AY = 35.0, 17.5
at("U9", AX, AY, 0)
# bias feedback (pins 61-63, top-left)
at(take(value="1M", nets=["BIASINV", "BIASOUT"]), 25.4, 8.0, 0)
at(take(value="1nF C0G", nets=["BIASINV", "BIASOUT"]), 25.4, 9.6, 0)
# top row caps (pins 49-60)
top = [("1uF", ["+2V5", "GND"]), ("100nF", ["+2V5", "GND"]),
       ("1uF", ["-2V5", "GND"]), ("100nF", ["-2V5", "GND"]),
       ("1uF", ["VCAP3", "-2V5"]), ("100nF", ["VCAP3", "-2V5"]),
       ("1uF", ["+2V5", "GND"]), ("100nF", ["+2V5", "GND"]),
       ("1uF", ["-2V5", "GND"]), ("100nF", ["-2V5", "GND"]),
       ("1uF", ["+3V3_D", "GND"]), ("100nF", ["+3V3_D", "GND"])]
small = [t for t in top if t[0] == "100nF"]; big = [t for t in top if t[0] != "100nF"]
for i, (v, n) in enumerate(small):          # 100 nF row nearest the pins
    at(take(value=v, nets=n), 29.6 + i * 1.55, 9.2, 90)
for i, (v, n) in enumerate(big):
    at(take(value=v, nets=n), 29.6 + i * 1.55, 6.2, 90)
at(take(value="10k", nets=["ADS_CLKSEL", "+3V3_D"]), 44.4, 8.6, 90)
# bottom row caps (pins 17-32)
bot = [("1uF", ["+2V5", "GND"]), ("100nF", ["+2V5", "GND"]),
       ("1uF", ["-2V5", "GND"]), ("100nF", ["-2V5", "GND"]),
       ("100nF", ["VREFP", "-2V5"]), ("1uF", ["VCAP4", "-2V5"]), ("1uF", ["VCAP2", "-2V5"])]
for i, (v, n) in enumerate(bot):
    at(take(value=v, nets=n), 30.0 + i * 1.55, 25.8, 90)
at(take(value="10uF", nets=["VREFP", "-2V5"]), 32.0, 29.4, 90)
at(take(value="100uF", nets=["VCAP1", "-2V5"]), 37.2, 29.8, 90)
# right side: DVDD decoupling and static pull resistors (pins 33-48)
at(take(value="1uF", nets=["+3V3_D", "GND"]), 43.4, 11.4, 0)
at(take(value="100nF", nets=["+3V3_D", "GND"]), 43.4, 13.0, 0)
pulls = [("10k", ["ADS_RESET", "+3V3_D"]), ("10k", ["ADS_PWDN", "+3V3_D"]), ("10k", ["ADS_CS", "+3V3_D"]),
         ("10k", ["ADS_START", "GND"]), ("10k", ["ADS_GPIO1", "GND"]), ("10k", ["ADS_GPIO2", "GND"]),
         ("10k", ["ADS_GPIO3", "GND"]), ("10k", ["ADS_GPIO4", "GND"])]
for i, (v, n) in enumerate(pulls):
    at(take(value=v, nets=n), 45.4, 15.0 + i * 1.5, 0)
series = [["M_SCLK", "ADS_SCLK"], ["M_DIN", "ADS_DIN"], ["M_DOUT", "ADS_DOUT"], ["M_CS", "ADS_CS"],
          ["M_START", "ADS_START"], ["M_RESET", "ADS_RESET"], ["M_PWDN", "ADS_PWDN"]]
for i, n in enumerate(series):
    at(take(value="100", nets=n), 50.4, 24.0 + i * 1.5, 0)

# ---------------------------------------------------------------- analog supplies
at("U5", 82.0, 6.0, 0)                                           # +3V3_D LDO
at(take(value="1uF", nets=["VBAT", "GND"]), 78.6, 6.0, 90)
at(take(value="10uF", nets=["+3V3_D", "GND"]), 85.6, 6.0, 90)
at("U6", 66.0, 6.0, 0)                                           # LM2664
at(take(value="1uF", nets=["+3V3_D", "GND"]), 70.0, 6.0, 90)
at(take(value="10uF", nets=["INV_CP", "INV_CN"]), 66.0, 2.6, 0)
at(take(value="10uF", nets=["-3V3_RAW", "GND"]), 62.0, 6.0, 90)
at("U7", 62.0, 13.0, 0)                                          # TPS72325 -2.5 V
at(take(value="2.2uF", nets=["-3V3_RAW", "GND"]), 58.4, 11.0, 90)
at(take(value="10nF", nets=["NR_NEG", "GND"]), 65.8, 15.2, 90)
at(take(value="2.2uF", nets=["-2V5", "GND"]), 58.4, 15.0, 90)
at(take(value="10uF", nets=["-2V5", "GND"]), 56.8, 15.0, 90)
at("U8", 74.0, 13.0, 0)                                          # TLV70025 +2.5 V
at(take(value="2.2uF", nets=["+3V3_D", "GND"]), 70.4, 13.0, 90)
at(take(value="2.2uF", nets=["+2V5", "GND"]), 77.6, 13.0, 90)
at(take(value="10uF", nets=["+2V5", "GND"]), 79.2, 13.0, 90)

# ---------------------------------------------------------------- power region (left bottom)
at("J1", 4.4, 47.0, 270)                                         # USB-C, opening to the left edge
at(take(value="5.1k", nets=["CC1", "GND"]), 12.2, 43.2, 0)
at(take(value="5.1k", nets=["CC2", "GND"]), 12.2, 50.8, 0)
at(take(value="10uF", nets=["VBUS", "GND"]), 11.0, 47.0, 90)
at("U1", 18.0, 47.0, 0)
at(take(value="2k", nets=["PROG", "GND"]), 14.4, 52.6, 0)
at(take(value="10uF", nets=["VBAT", "GND"]), 23.4, 47.0, 90)
at("D1", 7.0, 54.4, 180); at(take(value="1k", nets=["VBUS", "LED_CHRG"]), 11.4, 54.4, 0)
at("D2", 7.0, 57.0, 180); at(take(value="1k", nets=["VBUS", "LED_STDBY"]), 11.4, 57.0, 0)
at("SW1", 4.0, 64.0, 270)
at(take(value="100k", nets=["EN_SYS", "GND"]), 9.8, 64.0, 90)
at("J2", 7.0, 75.0, 0)                                           # battery, cable exits bottom edge
at("U2", 16.0, 70.0, 0)
at(take(value="100", nets=["VBAT", "DW_VCC"]), 16.0, 66.4, 0)
at(take(value="100nF", nets=["DW_VCC", "BAT_N"]), 19.4, 66.4, 90)
at(take(value="1k", nets=["DW_CS", "GND"]), 16.0, 73.6, 0)
at("Q1", 21.6, 70.0, 0)
at("U3", 26.0, 56.0, 0)                                          # MCU 3.3 V LDO
at(take(value="10uF", nets=["VBAT", "GND"]), 22.4, 56.0, 90)
at(take(value="10uF", nets=["3V3_MCU_LDO", "GND"]), 29.4, 56.0, 90)
at("U4", 26.0, 61.0, 0)                                          # reverse-blocking switch
at(take(value="10uF", nets=["+3V3_MCU", "GND"]), 29.4, 61.0, 90)
at(take(value="100nF", nets=["+3V3_MCU", "GND"]), 31.0, 61.0, 90)
at(take(value="1M", nets=["VBAT", "VBAT_SENSE"]), 27.0, 66.6, 0)
at(take(value="1M", nets=["VBAT_SENSE", "GND"]), 27.0, 68.2, 0)
at(take(value="100nF", nets=["VBAT_SENSE", "GND"]), 30.6, 67.4, 90)

# ---------------------------------------------------------------- digital: devkit sockets, I2C, sensors
J5_Y, J6_Y, PIN1_X = 44.0, 69.4, 95.0
at("J5", PIN1_X, J5_Y, 270)                 # pins run toward -x (checked in gen_pcb)
at("J6", PIN1_X, J6_Y, 270)
for i, n in enumerate([["I2C0_SDA", "+3V3_MCU"], ["I2C0_SCL", "+3V3_MCU"], ["I2C1_SDA", "+3V3_MCU"], ["I2C1_SCL", "+3V3_MCU"]]):
    at(take(value="4.7k", nets=n), 70.0 + i * 3.0, 50.0, 90)
at(take(value="100nF", nets=["+3V3_MCU", "GND"]), 90.0, 49.0, 90)
at("J7", 42.0, 76.6, 90); at("J8", 56.0, 76.6, 90); at("J9", 70.0, 76.6, 90)

# ---------------------------------------------------------------- test points and holes
tps = {p["ref"]: p["value"] for p in D.PARTS if p["sym"] == "TP"}
tp_xy = {"VBAT": (24.0, 77.0), "+3V3_MCU": (33.0, 52.0), "+3V3_D": (88.5, 6.0), "+2V5": (82.0, 16.0),
         "-2V5": (54.0, 18.0), "ADS_DRDY": (47.0, 33.5), "ADS_CLK": (44.0, 33.5)}
gnd_xy = [(31.0, 77.0), (91.0, 16.0)]
for r, v in tps.items():
    if v == "GND":
        at(r, *gnd_xy.pop(0))
    else:
        at(r, *tp_xy[v])
at("H1", 96.4, 3.6); at("H2", 3.6, 36.2); at("H3", 96.4, 76.4); at("H4", 36.4, 76.4)

missing = [p["ref"] for p in D.PARTS if p["ref"] not in P]
if missing:
    raise SystemExit(f"unplaced parts: {missing}")

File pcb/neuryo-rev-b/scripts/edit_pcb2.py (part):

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eline((0, H - r5), (0, r5)); earc((0, r5), (r5 * c, r5 * c), (r5, 0))
log('outline 77 x 50 mm: left corners R5 as the reference, right corners R1 (the XIAO pads reach the bottom right)')

# ================================================================== change 1: R27/C31 to SRB2 (pin 18), pin 17 open
# R27/C31 node (old SRB1 copper up to via 25.5,44.5) becomes SRB2; header SRB2 run from D5 IO4 onwards is removed;
# the old SRB2 run from via (26.25,42.5) to pin 18 is kept and joined to via (25.5,44.5) on B.Cu.
for s in kids(B, 'segment'):
    if nn(s) == 'SRB1':
        kid(s, 'net')[1:] = ['SRB2']
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             ((18.70, 43.82), (19.28, 43.82)), ((19.28, 43.82), (19.35, 43.75))):
    set_seg_net(a, b, 'SRB2_HDR')
path([(25.50, 44.50), (26.25, 43.75), (26.25, 42.50)], 'SRB2', 0.254, 'B.Cu')
log('change 1: REF -> R27 -> via 25.5,44.5 -> B.Cu -> via 26.25,42.5 -> old SRB2 run -> U4 pin 18; pin 17 has no copper')

# ================================================================== change 4: START low through R36 (10k) near the ADS1299
for a, b in (((54.85, 31.60), (56.00, 32.75)), ((76.72, 36.50), (76.75, 36.47)), ((75.25, 36.50), (76.72, 36.50))):
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# ---- I2C headers J6 (earlobe MAX30102) and J7 (BMI270): 1 GND, 2 3V3, 3 SDA, 4 SCL (pin 1 at the top); left of the
#      LM27762 block, joined pin to pin on F.Cu. Three B.Cu traces run down over the In2 VIN plane (x 62.6-63.5), step
#      left at y 20.6-21.6 and run down x 55.75-56.65 (over DVDD, then VIN) to vias beside the XIAO pads.
newfp('PinHeader_1x04_P2.54_TSW.kicad_mod', 'J6', 'MAX30102 earlobe', (58.3, 4.6), 270, 'F.Cu', {'1': 'GND', '2': 'XIAO_3V3', '3': 'I2C_SDA', '4': 'I2C_SCL'})
newfp('PinHeader_1x04_P2.54_TSW.kicad_mod', 'J7', 'BMI270', (61.3, 4.6), 270, 'F.Cu', {'1': 'GND', '2': 'XIAO_3V3', '3': 'I2C_SDA', '4': 'I2C_SCL'})
for k, n in ((2, 'XIAO_3V3'), (3, 'I2C_SDA'), (4, 'I2C_SCL')):
    seg(P('J6', k), P('J7', k), n, 0.4 if k == 2 else 0.254)
path([P('J7', 2), (63.5, P('J7', 2)[1]), (63.5, 21.6), (56.65, 21.6), (56.65, 41.5), (XP['12'][0], 41.5), (XP['12'][0], 43.0)], 'XIAO_3V3', 0.3, 'B.Cu')
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        kid(kid(t, 'effects'), 'justify')[1:] = [Sym('right'), Sym('bottom')]
        log('silkscreen', t[1], 'label moved left of its test point (J6 is now on its right)')
    if t[1] == 'REF SRB2':
        t[1] = 'REF  nc'; log('silkscreen REF SRB2 -> REF nc (header SRB2 pin no longer goes to the ADS1299)')
for t in list(kids(B, 'gr_text_box')):
    B.remove(t); log('delete bottom text box', t[1].strip())

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
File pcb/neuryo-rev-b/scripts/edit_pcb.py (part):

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move('D6', 73.4, 22.3, 0)                  # VBAT TVS (bottom side) beside J1 pin 2
move('C49', 73.2, 24.9, 0)                 # VBAT 4.7 uF (bottom side) beside J1 pin 2

# ------------------------------------------------------------------ 3. LM27762 EN+ (pin 12) and EN- (pin 8) off VIN -> AEN
def segs():
    return kids(B, 'segment')

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    set_net(pad(r, num)['el'], 'AEN')

# ------------------------------------------------------------------ 4. other net changes on kept parts
# change 1: R27/C31 node moves from SRB1 to SRB2; header SRB2 pin + D5 IO4 become SRB2_HDR
for r, num, new in (('R27', 2, 'SRB2'), ('C31', 1, 'SRB2'), ('J19', 2, 'SRB2_HDR'), ('D5', 5, 'SRB2_HDR')):
    set_net(pad(r, num)['el'], new)
for p in kids(fps('U4')[0], 'pad'):
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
